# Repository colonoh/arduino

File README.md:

# arduino
For all my Arduino code

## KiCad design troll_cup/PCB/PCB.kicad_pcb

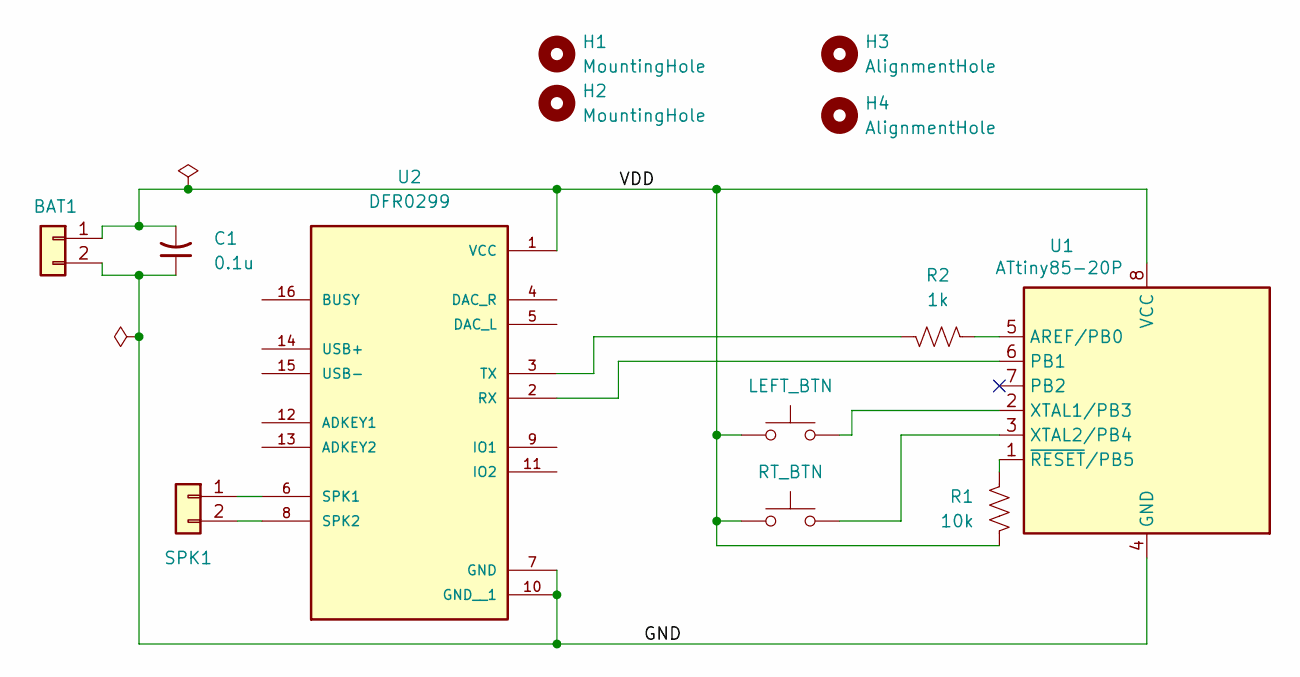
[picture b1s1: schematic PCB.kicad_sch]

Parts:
BAT1: TO_BATTERY; JST_PH_S2B-PH-K_1x02_P2.00mm_Horizontal
C1: 0.1u; C_Disc_D5.0mm_W2.5mm_P2.50mm
H1, H2: MountingHole; MountingHole_3.2mm_M3
H3, H4: AlignmentHole; MountingHole_2.5mm
R1: 10k; R_Axial_DIN0204_L3.6mm_D1.6mm_P5.08mm_Horizontal
R2: 1k; R_Axial_DIN0207_L6.3mm_D2.5mm_P7.62mm_Horizontal
SPK1: JST_PH_S2B-PH-K_1x02_P2.00mm_Horizontal
SW1: LEFT_BTN; Keypad 2
SW2: RT_BTN; Keypad 2
U1: ATtiny85-20P; DIP-8_W7.62mm
U2: DFR0299; MODULE_DFR0299

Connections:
/GND: BAT1.2, C1.1, U1.4 (GND), U2.7 (GND), U2.10 (GND__1)
/VDD: BAT1.1, C1.2, R1.1, SW1.2, SW2.2, U1.8 (VCC), U2.1 (VCC)
unnamed: SPK1.1, U2.6 (SPK1)
unnamed: SPK1.2, U2.8 (SPK2)
unnamed: R2.1, U1.5 (AREF/PB0)
unnamed: U1.6 (PB1), U2.2 (RX)
unnamed: SW1.1, U1.2 (XTAL1/PB3)
unnamed: SW2.1, U1.3 (XTAL2/PB4)
unnamed: R1.2, U1.1 (~RESET/PB5)
unnamed: R2.2, U2.3 (TX)

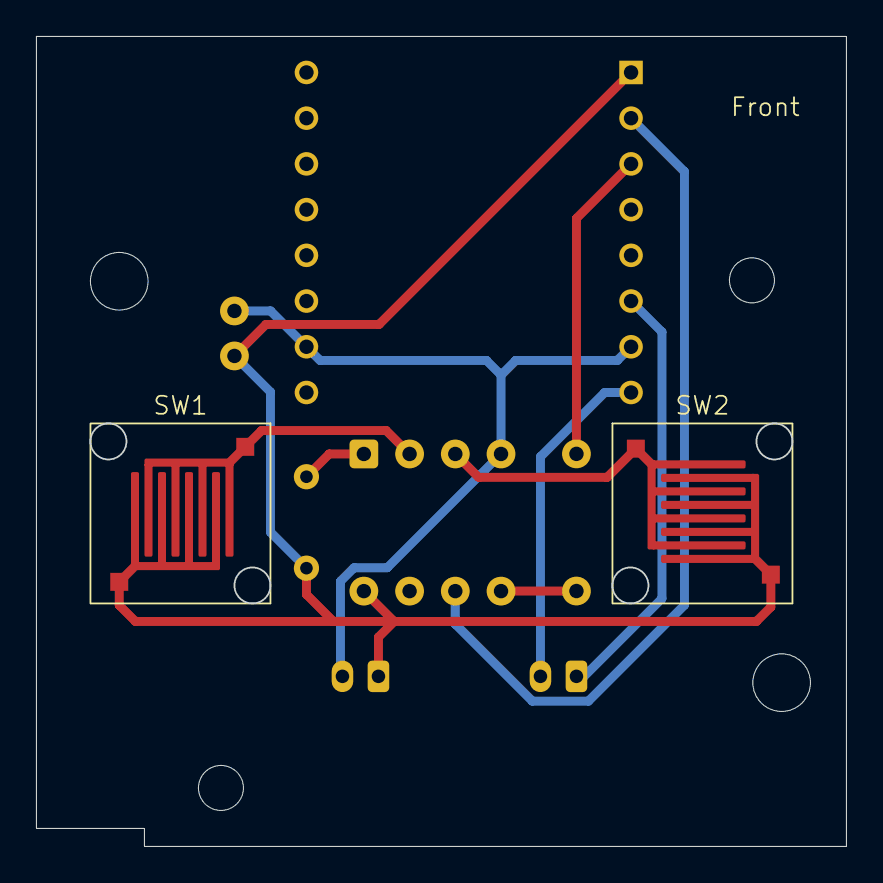
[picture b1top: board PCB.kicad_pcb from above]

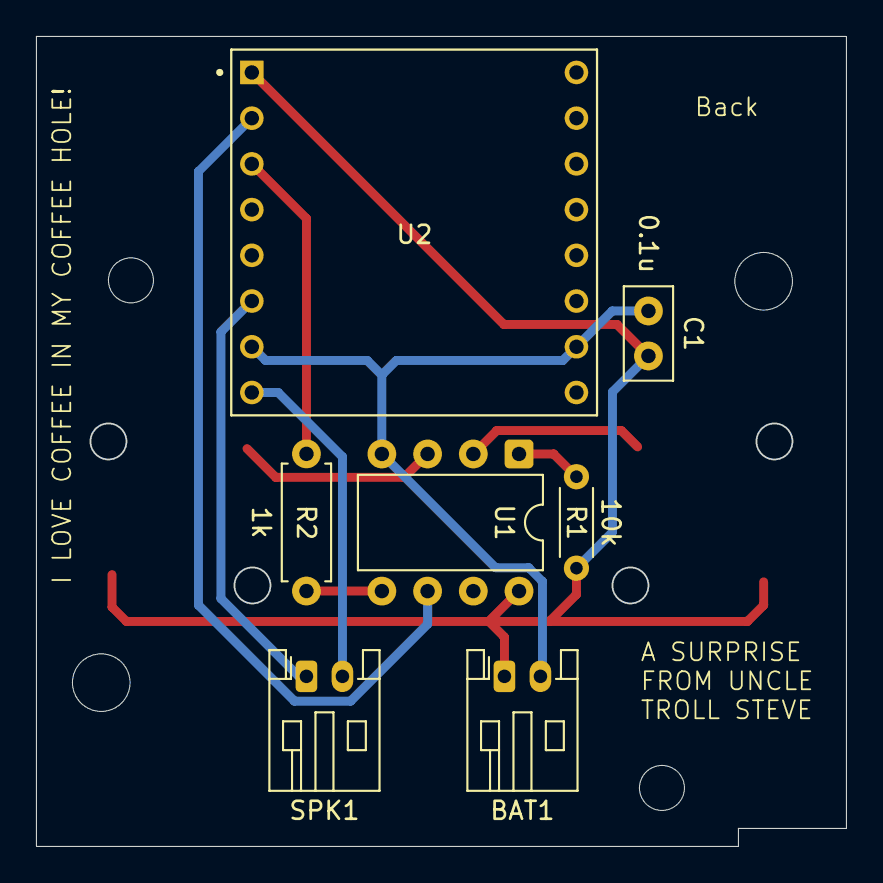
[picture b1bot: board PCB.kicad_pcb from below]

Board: 2 copper layers, 45.0 x 45.0 mm, 13 parts (7 on the bottom side), 10 nets.

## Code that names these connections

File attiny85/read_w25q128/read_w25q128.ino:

// Portable W25Q128 SPI code for ATTiny85 and ATTiny1614
// ATTiny85: Uses bit-banged SPI (USI-based SPI libraries don't work reliably)
// ATTiny1614: Uses hardware SPI

#if defined(__AVR_ATtiny85__)
  // ATTiny85 - bit-bang SPI
  #define CS_PIN 3   // PB3 = physical pin 2
  #define LED_PIN 4  // PB4 = physical pin 3
  #define MOSI_PIN 0 // PB0 = physical pin 5
  #define MISO_PIN 1 // PB1 = physical pin 6
  #define SCK_PIN 2  // PB2 = physical pin 7
  #define USE_BITBANG
#else
  // ATTiny1614 - hardware SPI
  #include <SPI.h>
  #define CS_PIN 10  // Adjust for your ATTiny1614 wiring
  #define LED_PIN 7  // Adjust for your ATTiny1614 wiring
#endif

uint8_t spiTransfer(uint8_t data) {
#ifdef USE_BITBANG
  uint8_t result = 0;
  for(int i=7; i>=0; i--) {
    digitalWrite(MOSI_PIN, (data & (1<<i)) ? HIGH : LOW);
    delayMicroseconds(1);

    digitalWrite(SCK_PIN, HIGH);
    delayMicroseconds(1);

    if(digitalRead(MISO_PIN)) {
      result |= (1<<i);
    }

    digitalWrite(SCK_PIN, LOW);
    delayMicroseconds(1);
  }
  return result;
#else
  return SPI.transfer(data);
#endif
}

void spiBegin() {
#ifdef USE_BITBANG
  pinMode(CS_PIN, OUTPUT);
  pinMode(MOSI_PIN, OUTPUT);
  pinMode(MISO_PIN, INPUT);
  pinMode(SCK_PIN, OUTPUT);
  digitalWrite(CS_PIN, HIGH);
  digitalWrite(SCK_PIN, LOW);
  digitalWrite(MOSI_PIN, LOW);
#else
  pinMode(CS_PIN, OUTPUT);
  digitalWrite(CS_PIN, HIGH);
  SPI.begin();
  SPI.setDataMode(SPI_MODE0);
  SPI.setBitOrder(MSBFIRST);
#endif
}

// Read audio from flash and flash LED based on amplitude
void playAudioWithLED(uint32_t startAddr, uint32_t numSamples) {
  // Start continuous read from flash
  digitalWrite(CS_PIN, LOW);
  delayMicroseconds(1);
  spiTransfer(0x03);  // Read Data command
  spiTransfer((startAddr >> 16) & 0xFF);
  spiTransfer((startAddr >> 8) & 0xFF);
  spiTransfer(startAddr & 0xFF);

  uint16_t avg = 0;
  const uint8_t threshold = 30;  // Adjust for sensitivity

  for (uint32_t i = 0; i < numSamples; i++) {
    uint8_t sample = spiTransfer(0x00);

    // Convert to amplitude (distance from center 128)
    uint8_t amplitude = (sample > 128) ? (sample - 128) : (128 - sample);

    // Simple IIR low-pass filter: avg = 7/8 * avg + 1/8 * amplitude
    avg = ((avg * 7) + (amplitude * 8)) >> 3;

    // Flash LED based on filtered amplitude
    digitalWrite(LED_PIN, avg > threshold);

    // Delay for ~16kHz sample rate (62.5us per sample)
    delayMicroseconds(62);
  }

  digitalWrite(CS_PIN, HIGH);
  digitalWrite(LED_PIN, LOW);
}

void setup() {
  // Startup blink
  pinMode(LED_PIN, OUTPUT);
  digitalWrite(LED_PIN, HIGH);
  delay(1000);
  digitalWrite(LED_PIN, LOW);

  spiBegin();
  delay(10);

  // Read W25Q128 JEDEC ID
  digitalWrite(CS_PIN, LOW);
  delayMicroseconds(1);
  spiTransfer(0x9F);  // Read JEDEC ID command
  uint8_t mfg = spiTransfer(0x00);
  uint8_t type = spiTransfer(0x00);
  uint8_t capacity = spiTransfer(0x00);
  delayMicroseconds(1);
  digitalWrite(CS_PIN, HIGH);

  // Expected: mfg=0xEF (Winbond), type=0x40, capacity=0x18

  // if (mfg == 0xEF) {
  // if (type == 0x40) {
  if (capacity == 0x18) {
    // Success - fast blink 10 times
    for(int i=0; i<10; i++) {
      digitalWrite(LED_PIN, HIGH);
      delay(100);
      digitalWrite(LED_PIN, LOW);
      delay(100);
    }

    delay(1000);

    // Test: Read audio data and flash LED based on amplitude
    // Assumes 8-bit unsigned PCM at 16kHz starting at address 0
    playAudioWithLED(0x0000b6, 16000 * 5);  // 5 seconds of audio

    delay(1000);

    // Send Deep Power-Down command
    digitalWrite(CS_PIN, LOW);
    delayMicroseconds(1);
    spiTransfer(0xB9);  // Deep Power-Down command
    delayMicroseconds(1);
    digitalWrite(CS_PIN, HIGH);

    // Wait for chip to enter deep power-down (tDP = 3us typical)
    delayMicroseconds(10);

    // Bring pins low to ensure low power usage while powered down
    digitalWrite(MOSI_PIN, LOW);
    digitalWrite(SCK_PIN, LOW);
    digitalWrite(MISO_PIN, LOW);

    // Final LED blink to show power-down sent
    digitalWrite(LED_PIN, HIGH);
    delay(500);
    digitalWrite(LED_PIN, LOW);

    // Infinite loop - do nothing, measure current now
    while(1) {
      delay(1000);
    }

  } else {
    // Fail - slow blink forever
    while(1) {
      digitalWrite(LED_PIN, HIGH);
      delay(500);
      digitalWrite(LED_PIN, LOW);
      delay(500);
    }
  }

}

void loop() {
  // Should never get here due to while(1) in setup
}

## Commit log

2025-01-25 Final version of the code
2025-01-25 Add a screenshot
2025-01-25 Add screenshot to readme
2025-01-25 Add a flowchart
2025-01-25 Add the screenshot to the readme
2025-05-17 Initial troll cup code
2025-05-17 Move it out of the folder
2025-05-17 Just kidding
2025-05-17 Get mad!
    Add delays cause the myDFPlayer.read() doesn't seem too reliable and sometimes it starts playing before it's finished
2025-05-17 Autoformat
2025-05-17 Get folder counts
2025-05-17 Choose randomly
2025-05-17 Remove debugging info
2025-05-17 Switch to SoftwareSerial
    ATTiny85 doesn't have uart built in so we'll have to use a software-base serial
2025-05-18 Actual values for pins
2025-05-18 Remove serial stuff
2025-05-18 Add Kicad files
2025-05-18 Organize schematic
2025-05-26 Do stuff in kicad
2025-05-26 New footprint
2025-05-26 Added traces
2025-06-07 Oops! The board has these pins reversed!
2025-12-13 Bit-banging because can't get SPI to work
2025-12-13 Checking all the different values
2025-12-13 Add going into low power mode
    Note the need to drive the w25q128's pins low otherwise it uses 7-12uA
2025-12-13 Remove cause unnecessary
2025-12-14 Move file
2025-12-15 Test LED based on audio data
2025-12-17 Read flash data and flash LED
2025-12-17 Plays audio but slow
2025-12-17 Use a timer and its interrupt instead of delay
2025-12-17 Add basic amp shutdown
2025-12-17 Put it to sleep
2025-12-17 Put flash chip into sleep and pins to LOW
    except CS
2025-12-17 Eliminate startup pop by keeping amp off for a bit
2025-12-17 Sleep and wake via button to play audio
2025-12-17 Cleanup debugging/unneeded code
2025-12-17 Minor refactor
2025-12-17 Renaming variables for readability
2025-12-18 Use playing var to avoid 32-bit non-atomic read race condition
2025-12-20 Add files
2025-12-25 Add comments
2025-12-25 Move SPI comand into the same place
2026-01-02 Update pin assignments
2026-01-02 Add track list and picking at random
2026-01-02 Add one-off intro song when powered up
2026-01-02 Rename sleep function
2026-01-03 Fix typos
2026-01-03 Reduce the volume by 50%
